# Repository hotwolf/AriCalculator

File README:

AriCalculator
=============
A homemade pocket calculator.

Directories:
============
|
+-Hardware              - Everything needed to build AriCalculator RevA, RevB,
                          and RevC
|
+-Software              - Source files (ASM and Forth) of the calculators
                          firmware
|
+-Tools                 - Tools written for the development of the AriCalculator
|
+-Subprojects           - Repository clones of the projects that AriCalculator
                          is based on

The AriCalculator software is distributed in the hope that it will be useful,
but WITHOUT ANY WARRANTY; without even the implied warranty of
MERCHANTABILITY or FITNESS FOR A PARTICULAR PURPOSE.  See the
GNU General Public License for more details.

You should have received a copy of the GNU General Public License
along with the AriCalculator software. If not, see
<http://www.gnu.org/licenses/>.

The hardware design of the Aricalculator project is licensed under a Creative
Commons Attribution-ShareAlike 3.0 Unported License
(http://creativecommons.org/licenses/by-sa/3.0/).

Hardware RevC uses Kicad library components by Walter Lain which are licensed
under a Creative Commons Attribution-ShareAlike 3.0 License 
(http://creativecommons.org/licenses/by-sa/3.0/).

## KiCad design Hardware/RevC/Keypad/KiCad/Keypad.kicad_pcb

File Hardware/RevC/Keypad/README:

Keypad
======
A general purpose key pad PCB

Directories:
============
|
+-KiCad			- KiCad project file, schematic, layout, and libraries
|
+-Gerber                - Gerber files for manufacturing

This work is licensed under a Creative Commons Attribution-ShareAlike 3.0
Unported License (http://creativecommons.org/licenses/by-sa/3.0/).

AriCalculator RevC and the Keypad use Kicad library components by Walter Lain
which are licensedunder a Creative Commons Attribution-ShareAlike 3.0 License 
(http://creativecommons.org/licenses/by-sa/3.0/).

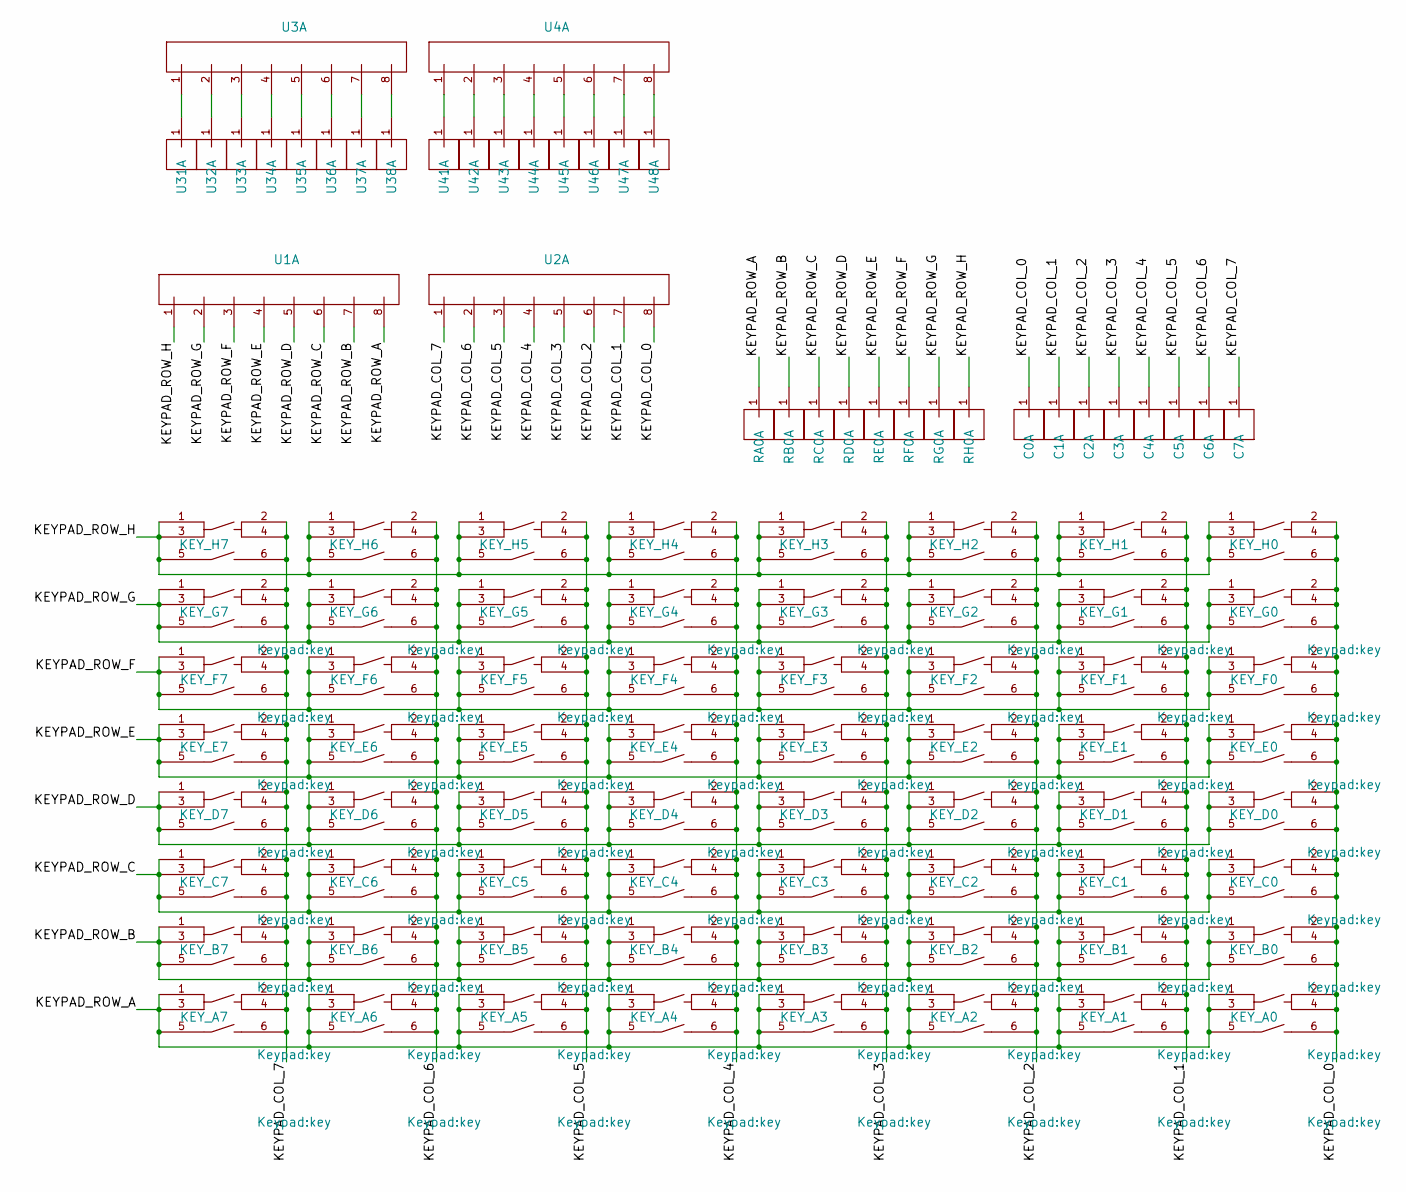
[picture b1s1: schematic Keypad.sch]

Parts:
C0, C1, C2, C3, C4, C5, C6, C7: PIN_STRIP_1; Connected_Pad
KEY_A0, KEY_A1, KEY_A2, KEY_A3, KEY_A4, KEY_A5, KEY_A6, KEY_A7: KEY; key
KEY_B0, KEY_B1, KEY_B2, KEY_B3, KEY_B4, KEY_B5, KEY_B6, KEY_B7: KEY; key
KEY_C0, KEY_C1, KEY_C2, KEY_C3, KEY_C4, KEY_C5, KEY_C6, KEY_C7: KEY; key
KEY_D0, KEY_D1, KEY_D2, KEY_D3, KEY_D4, KEY_D5, KEY_D6, KEY_D7: KEY; key
KEY_E0, KEY_E1, KEY_E2, KEY_E3, KEY_E4, KEY_E5, KEY_E6, KEY_E7: KEY; key
KEY_F0, KEY_F1, KEY_F2, KEY_F3, KEY_F4, KEY_F5, KEY_F6, KEY_F7: KEY; key
KEY_G0, KEY_G1, KEY_G2, KEY_G3, KEY_G4, KEY_G5, KEY_G6, KEY_G7: KEY; key
KEY_H0, KEY_H1, KEY_H2, KEY_H3, KEY_H4, KEY_H5, KEY_H6, KEY_H7: KEY; key
RA0: PIN_STRIP_1; Connected_Pad
RB0: PIN_STRIP_1; Connected_Pad
RC0: PIN_STRIP_1; Connected_Pad
RD0: PIN_STRIP_1; Connected_Pad
RE0: PIN_STRIP_1; Connected_Pad
RF0: PIN_STRIP_1; Connected_Pad
RG0: PIN_STRIP_1; Connected_Pad
RH0: PIN_STRIP_1; Connected_Pad
U1, U2, U3, U4: PIN_STRIP_8; pin_strip_8
U31, U32, U33, U34, U35, U36, U37, U38, U41, U42, U43, U44, U45, U46, U47, U48: PIN_STRIP_1; Connected_Pad

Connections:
/KEYPAD_COL_0: C0.1, KEY_A0.2, KEY_A0.4, KEY_A0.6, KEY_B0.2, KEY_B0.4, KEY_B0.6, KEY_C0.2, KEY_C0.4, KEY_C0.6, KEY_D0.2, KEY_D0.4, KEY_D0.6, KEY_E0.2, KEY_E0.4, KEY_E0.6, KEY_F0.2, KEY_F0.4, KEY_F0.6, KEY_G0.2, KEY_G0.4, KEY_G0.6, KEY_H0.2, KEY_H0.4, KEY_H0.6, U2.8
/KEYPAD_COL_1: C1.1, KEY_A1.2, KEY_A1.4, KEY_A1.6, KEY_B1.2, KEY_B1.4, KEY_B1.6, KEY_C1.2, KEY_C1.4, KEY_C1.6, KEY_D1.2, KEY_D1.4, KEY_D1.6, KEY_E1.2, KEY_E1.4, KEY_E1.6, KEY_F1.2, KEY_F1.4, KEY_F1.6, KEY_G1.2, KEY_G1.4, KEY_G1.6, KEY_H1.2, KEY_H1.4, KEY_H1.6, U2.7
/KEYPAD_COL_2: C2.1, KEY_A2.2, KEY_A2.4, KEY_A2.6, KEY_B2.2, KEY_B2.4, KEY_B2.6, KEY_C2.2, KEY_C2.4, KEY_C2.6, KEY_D2.2, KEY_D2.4, KEY_D2.6, KEY_E2.2, KEY_E2.4, KEY_E2.6, KEY_F2.2, KEY_F2.4, KEY_F2.6, KEY_G2.2, KEY_G2.4, KEY_G2.6, KEY_H2.2, KEY_H2.4, KEY_H2.6, U2.6
/KEYPAD_COL_3: C3.1, KEY_A3.2, KEY_A3.4, KEY_A3.6, KEY_B3.2, KEY_B3.4, KEY_B3.6, KEY_C3.2, KEY_C3.4, KEY_C3.6, KEY_D3.2, KEY_D3.4, KEY_D3.6, KEY_E3.2, KEY_E3.4, KEY_E3.6, KEY_F3.2, KEY_F3.4, KEY_F3.6, KEY_G3.2, KEY_G3.4, KEY_G3.6, KEY_H3.2, KEY_H3.4, KEY_H3.6, U2.5
/KEYPAD_COL_4: C4.1, KEY_A4.2, KEY_A4.4, KEY_A4.6, KEY_B4.2, KEY_B4.4, KEY_B4.6, KEY_C4.2, KEY_C4.4, KEY_C4.6, KEY_D4.2, KEY_D4.4, KEY_D4.6, KEY_E4.2, KEY_E4.4, KEY_E4.6, KEY_F4.2, KEY_F4.4, KEY_F4.6, KEY_G4.2, KEY_G4.4, KEY_G4.6, KEY_H4.2, KEY_H4.4, KEY_H4.6, U2.4
/KEYPAD_COL_5: C5.1, KEY_A5.2, KEY_A5.4, KEY_A5.6, KEY_B5.2, KEY_B5.4, KEY_B5.6, KEY_C5.2, KEY_C5.4, KEY_C5.6, KEY_D5.2, KEY_D5.4, KEY_D5.6, KEY_E5.2, KEY_E5.4, KEY_E5.6, KEY_F5.2, KEY_F5.4, KEY_F5.6, KEY_G5.2, KEY_G5.4, KEY_G5.6, KEY_H5.2, KEY_H5.4, KEY_H5.6, U2.3
/KEYPAD_COL_6: C6.1, KEY_A6.2, KEY_A6.4, KEY_A6.6, KEY_B6.2, KEY_B6.4, KEY_B6.6, KEY_C6.2, KEY_C6.4, KEY_C6.6, KEY_D6.2, KEY_D6.4, KEY_D6.6, KEY_E6.2, KEY_E6.4, KEY_E6.6, KEY_F6.2, KEY_F6.4, KEY_F6.6, KEY_G6.2, KEY_G6.4, KEY_G6.6, KEY_H6.2, KEY_H6.4, KEY_H6.6, U2.2
/KEYPAD_COL_7: C7.1, KEY_A7.2, KEY_A7.4, KEY_A7.6, KEY_B7.2, KEY_B7.4, KEY_B7.6, KEY_C7.2, KEY_C7.4, KEY_C7.6, KEY_D7.2, KEY_D7.4, KEY_D7.6, KEY_E7.2, KEY_E7.4, KEY_E7.6, KEY_F7.2, KEY_F7.4, KEY_F7.6, KEY_G7.2, KEY_G7.4, KEY_G7.6, KEY_H7.2, KEY_H7.4, KEY_H7.6, U2.1
/KEYPAD_ROW_A: KEY_A0.1, KEY_A0.3, KEY_A0.5, KEY_A1.1, KEY_A1.3, KEY_A1.5, KEY_A2.1, KEY_A2.3, KEY_A2.5, KEY_A3.1, KEY_A3.3, KEY_A3.5, KEY_A4.1, KEY_A4.3, KEY_A4.5, KEY_A5.1, KEY_A5.3, KEY_A5.5, KEY_A6.1, KEY_A6.3, KEY_A6.5, KEY_A7.1, KEY_A7.3, KEY_A7.5, RA0.1, U1.8
/KEYPAD_ROW_B: KEY_B0.1, KEY_B0.3, KEY_B0.5, KEY_B1.1, KEY_B1.3, KEY_B1.5, KEY_B2.1, KEY_B2.3, KEY_B2.5, KEY_B3.1, KEY_B3.3, KEY_B3.5, KEY_B4.1, KEY_B4.3, KEY_B4.5, KEY_B5.1, KEY_B5.3, KEY_B5.5, KEY_B6.1, KEY_B6.3, KEY_B6.5, KEY_B7.1, KEY_B7.3, KEY_B7.5, RB0.1, U1.7
/KEYPAD_ROW_C: KEY_C0.1, KEY_C0.3, KEY_C0.5, KEY_C1.1, KEY_C1.3, KEY_C1.5, KEY_C2.1, KEY_C2.3, KEY_C2.5, KEY_C3.1, KEY_C3.3, KEY_C3.5, KEY_C4.1, KEY_C4.3, KEY_C4.5, KEY_C5.1, KEY_C5.3, KEY_C5.5, KEY_C6.1, KEY_C6.3, KEY_C6.5, KEY_C7.1, KEY_C7.3, KEY_C7.5, RC0.1, U1.6
/KEYPAD_ROW_D: KEY_D0.1, KEY_D0.3, KEY_D0.5, KEY_D1.1, KEY_D1.3, KEY_D1.5, KEY_D2.1, KEY_D2.3, KEY_D2.5, KEY_D3.1, KEY_D3.3, KEY_D3.5, KEY_D4.1, KEY_D4.3, KEY_D4.5, KEY_D5.1, KEY_D5.3, KEY_D5.5, KEY_D6.1, KEY_D6.3, KEY_D6.5, KEY_D7.1, KEY_D7.3, KEY_D7.5, RD0.1, U1.5
/KEYPAD_ROW_E: KEY_E0.1, KEY_E0.3, KEY_E0.5, KEY_E1.1, KEY_E1.3, KEY_E1.5, KEY_E2.1, KEY_E2.3, KEY_E2.5, KEY_E3.1, KEY_E3.3, KEY_E3.5, KEY_E4.1, KEY_E4.3, KEY_E4.5, KEY_E5.1, KEY_E5.3, KEY_E5.5, KEY_E6.1, KEY_E6.3, KEY_E6.5, KEY_E7.1, KEY_E7.3, KEY_E7.5, RE0.1, U1.4
/KEYPAD_ROW_F: KEY_F0.1, KEY_F0.3, KEY_F0.5, KEY_F1.1, KEY_F1.3, KEY_F1.5, KEY_F2.1, KEY_F2.3, KEY_F2.5, KEY_F3.1, KEY_F3.3, KEY_F3.5, KEY_F4.1, KEY_F4.3, KEY_F4.5, KEY_F5.1, KEY_F5.3, KEY_F5.5, KEY_F6.1, KEY_F6.3, KEY_F6.5, KEY_F7.1, KEY_F7.3, KEY_F7.5, RF0.1, U1.3
/KEYPAD_ROW_G: KEY_G0.1, KEY_G0.3, KEY_G0.5, KEY_G1.1, KEY_G1.3, KEY_G1.5, KEY_G2.1, KEY_G2.3, KEY_G2.5, KEY_G3.1, KEY_G3.3, KEY_G3.5, KEY_G4.1, KEY_G4.3, KEY_G4.5, KEY_G5.1, KEY_G5.3, KEY_G5.5, KEY_G6.1, KEY_G6.3, KEY_G6.5, KEY_G7.1, KEY_G7.3, KEY_G7.5, RG0.1, U1.2
/KEYPAD_ROW_H: KEY_H0.1, KEY_H0.3, KEY_H0.5, KEY_H1.1, KEY_H1.3, KEY_H1.5, KEY_H2.1, KEY_H2.3, KEY_H2.5, KEY_H3.1, KEY_H3.3, KEY_H3.5, KEY_H4.1, KEY_H4.3, KEY_H4.5, KEY_H5.1, KEY_H5.3, KEY_H5.5, KEY_H6.1, KEY_H6.3, KEY_H6.5, KEY_H7.1, KEY_H7.3, KEY_H7.5, RH0.1, U1.1
unnamed: U3.1, U31.1
unnamed: U3.2, U32.1
unnamed: U3.3, U33.1
unnamed: U3.4, U34.1
unnamed: U3.5, U35.1
unnamed: U3.6, U36.1
unnamed: U3.7, U37.1
unnamed: U3.8, U38.1
unnamed: U4.1, U41.1
unnamed: U4.2, U42.1
unnamed: U4.3, U43.1
unnamed: U4.4, U44.1
unnamed: U4.5, U45.1
unnamed: U4.6, U46.1
unnamed: U4.7, U47.1
unnamed: U4.8, U48.1

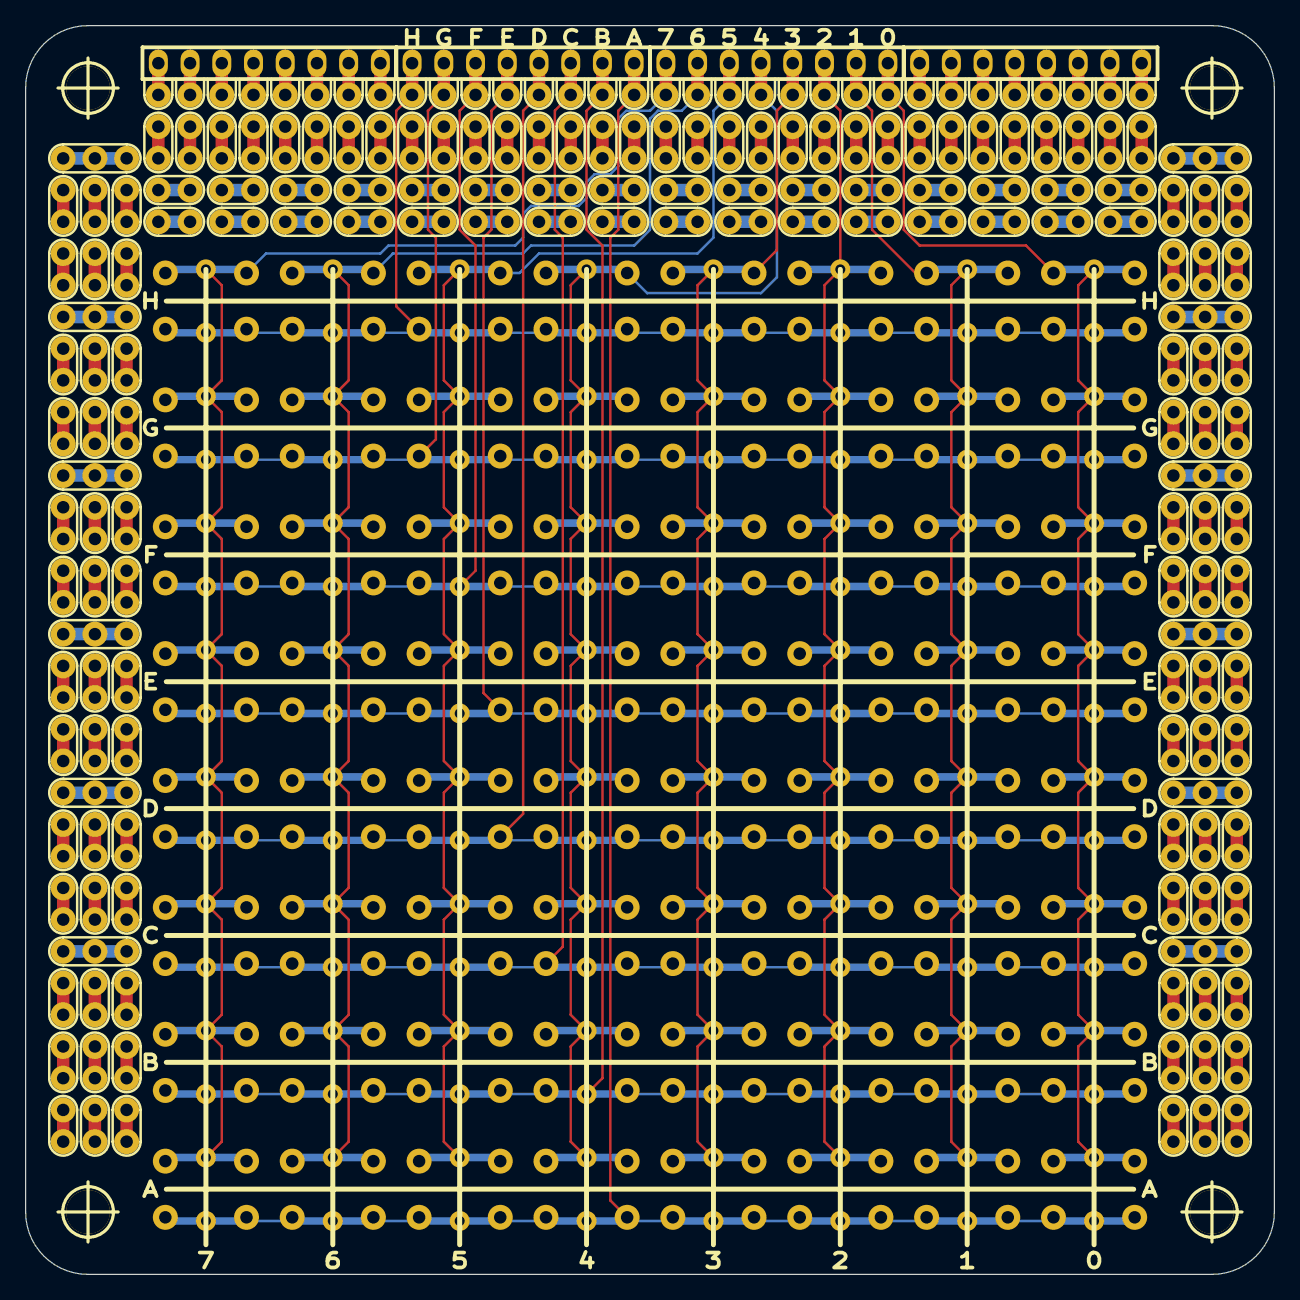
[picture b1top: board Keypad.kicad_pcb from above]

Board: 2 copper layers, 100.0 x 100.0 mm, 104 parts (0 on the bottom side), 32 nets.

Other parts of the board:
hole_3mm5, hole_3mm5#2, hole_3mm5#3, hole_3mm5#4: VAL**; hole_3mm5

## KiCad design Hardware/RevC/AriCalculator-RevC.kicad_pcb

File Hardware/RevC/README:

AriCalculator
=============
A homemade pocket calculator.

RevC is a redesign of the AriCalculator which breaks compatibility with the 
previous revisions. It is build with a single PCB instead of a combination of
S12G-Mini-EVB and millede base PCB. RevC has 38 keys (instead of 30) and
features an expansion port (SPI). All firmware development of the AriCalculator 
will be done on RevC. 

Directories:
============
|
+-Case   	        - Design files of the 3D printed case
|
+-Enclosure	        - Design files of the enclosure (for laser cutting)
|
+-PCB		        - Design files of the calculators PCB
|
+-Kepad		        - Design files of a plain key pad for debug purposes

|
+-KiCad			- KiCad project file, schematic, layout, and libraries
|
+-Gerber                - Gerber files for manufacturing

Files:
======
|
+-AriCalculator-RevC Schematic.pdf      - Schematic
|
+-AriCalculator-RevC BOM.txt            - Bill of materials
|
+-AriCalculator-RevC Assembly Plan.pdf  - Shows the location of all components
                                          to be assembled

This work is licensed under a Creative Commons Attribution-ShareAlike 3.0
Unported License (http://creativecommons.org/licenses/by-sa/3.0/).

AriCalculator RevC and the Keypad use Kicad library components by Walter Lain
which are licensedunder a Creative Commons Attribution-ShareAlike 3.0 License 
(http://creativecommons.org/licenses/by-sa/3.0/).

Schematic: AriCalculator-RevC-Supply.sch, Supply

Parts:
BAT1, BAT2: AAA-BATTERY
C3: 4.7uF
C4: 10uF
IC2: MCP1640
L1: 4.7uH
R9: 820K
R10: 470K
SW1: POWER SWITCH

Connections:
3V3: C4.1, IC2.5 (VOUT), R9.1; also elsewhere on the board
+BATT: C3.1, IC2.3 (EN), IC2.6 (VIN), L1.2, SW1.2; also elsewhere on the board
GND: BAT2.2, C3.2, C4.2, IC2.2 (GND), R10.1, SW1.1; also elsewhere on the board
unnamed: IC2.4 (VFB), R9.2, R10.2
unnamed: IC2.1 (SW), L1.1
unnamed: BAT1.1, SW1.3
unnamed: BAT1.2, BAT2.1

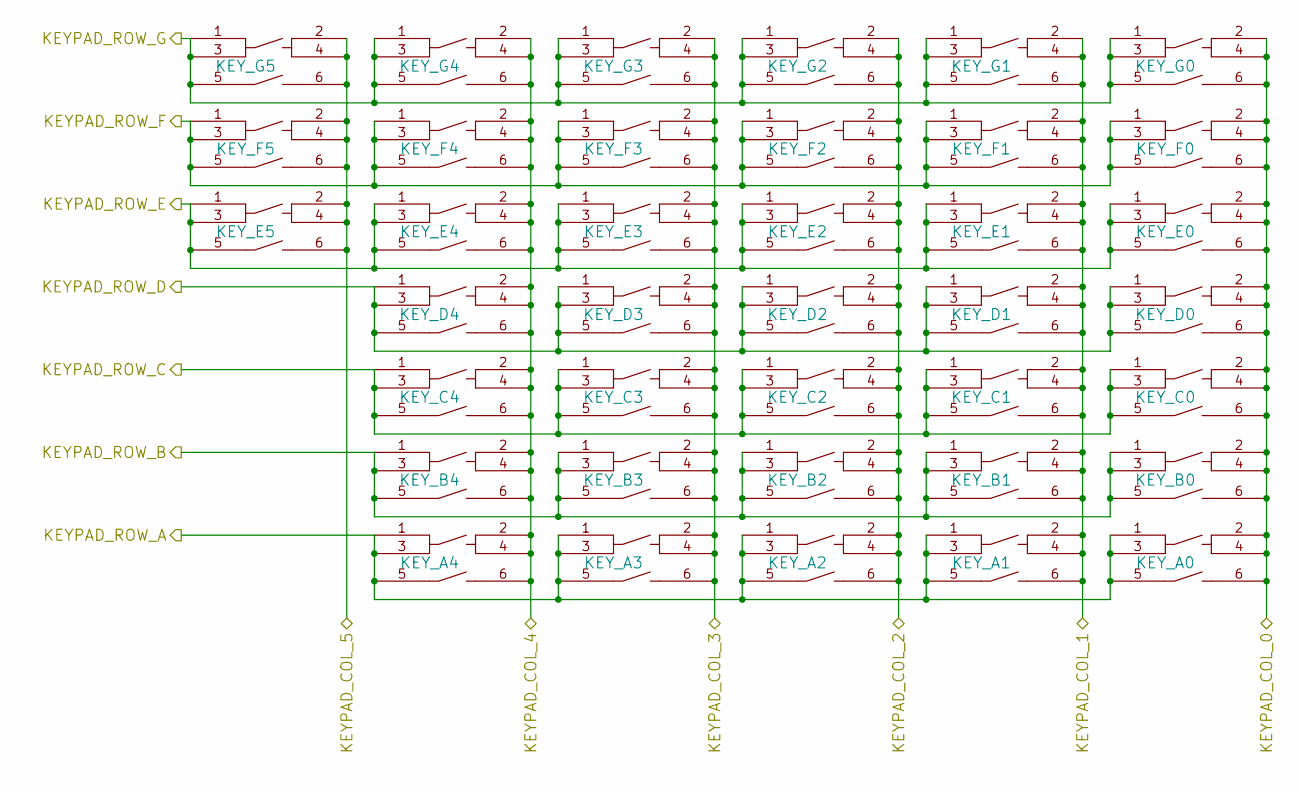
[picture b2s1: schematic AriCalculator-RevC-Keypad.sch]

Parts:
KEY_A0, KEY_A1, KEY_A2, KEY_A3, KEY_A4: KEY
KEY_B0, KEY_B1, KEY_B2, KEY_B3, KEY_B4: KEY
KEY_C0, KEY_C1, KEY_C2, KEY_C3, KEY_C4: KEY
KEY_D0, KEY_D1, KEY_D2, KEY_D3, KEY_D4: KEY
KEY_E0, KEY_E1, KEY_E2, KEY_E3, KEY_E4, KEY_E5: KEY
KEY_F0, KEY_F1, KEY_F2, KEY_F3, KEY_F4, KEY_F5: KEY
KEY_G0, KEY_G1, KEY_G2, KEY_G3, KEY_G4, KEY_G5: KEY

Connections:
/Keypad/KEYPAD_COL_0: KEY_A0.2, KEY_A0.4, KEY_A0.6, KEY_B0.2, KEY_B0.4, KEY_B0.6, KEY_C0.2, KEY_C0.4, KEY_C0.6, KEY_D0.2, KEY_D0.4, KEY_D0.6, KEY_E0.2, KEY_E0.4, KEY_E0.6, KEY_F0.2, KEY_F0.4, KEY_F0.6, KEY_G0.2, KEY_G0.4, KEY_G0.6; also elsewhere on the board
/Keypad/KEYPAD_COL_1: KEY_A1.2, KEY_A1.4, KEY_A1.6, KEY_B1.2, KEY_B1.4, KEY_B1.6, KEY_C1.2, KEY_C1.4, KEY_C1.6, KEY_D1.2, KEY_D1.4, KEY_D1.6, KEY_E1.2, KEY_E1.4, KEY_E1.6, KEY_F1.2, KEY_F1.4, KEY_F1.6, KEY_G1.2, KEY_G1.4, KEY_G1.6; also elsewhere on the board
/Keypad/KEYPAD_COL_2: KEY_A2.2, KEY_A2.4, KEY_A2.6, KEY_B2.2, KEY_B2.4, KEY_B2.6, KEY_C2.2, KEY_C2.4, KEY_C2.6, KEY_D2.2, KEY_D2.4, KEY_D2.6, KEY_E2.2, KEY_E2.4, KEY_E2.6, KEY_F2.2, KEY_F2.4, KEY_F2.6, KEY_G2.2, KEY_G2.4, KEY_G2.6; also elsewhere on the board
/Keypad/KEYPAD_COL_3: KEY_A3.2, KEY_A3.4, KEY_A3.6, KEY_B3.2, KEY_B3.4, KEY_B3.6, KEY_C3.2, KEY_C3.4, KEY_C3.6, KEY_D3.2, KEY_D3.4, KEY_D3.6, KEY_E3.2, KEY_E3.4, KEY_E3.6, KEY_F3.2, KEY_F3.4, KEY_F3.6, KEY_G3.2, KEY_G3.4, KEY_G3.6; also elsewhere on the board
/Keypad/KEYPAD_COL_4: KEY_A4.2, KEY_A4.4, KEY_A4.6, KEY_B4.2, KEY_B4.4, KEY_B4.6, KEY_C4.2, KEY_C4.4, KEY_C4.6, KEY_D4.2, KEY_D4.4, KEY_D4.6, KEY_E4.2, KEY_E4.4, KEY_E4.6, KEY_F4.2, KEY_F4.4, KEY_F4.6, KEY_G4.2, KEY_G4.4, KEY_G4.6; also elsewhere on the board
/Keypad/KEYPAD_COL_5: KEY_E5.2, KEY_E5.4, KEY_E5.6, KEY_F5.2, KEY_F5.4, KEY_F5.6, KEY_G5.2, KEY_G5.4, KEY_G5.6; also elsewhere on the board
/Keypad/KEYPAD_ROW_A: KEY_A0.1, KEY_A0.3, KEY_A0.5, KEY_A1.1, KEY_A1.3, KEY_A1.5, KEY_A2.1, KEY_A2.3, KEY_A2.5, KEY_A3.1, KEY_A3.3, KEY_A3.5, KEY_A4.1, KEY_A4.3, KEY_A4.5; also elsewhere on the board
/Keypad/KEYPAD_ROW_B: KEY_B0.1, KEY_B0.3, KEY_B0.5, KEY_B1.1, KEY_B1.3, KEY_B1.5, KEY_B2.1, KEY_B2.3, KEY_B2.5, KEY_B3.1, KEY_B3.3, KEY_B3.5, KEY_B4.1, KEY_B4.3, KEY_B4.5; also elsewhere on the board
/Keypad/KEYPAD_ROW_C: KEY_C0.1, KEY_C0.3, KEY_C0.5, KEY_C1.1, KEY_C1.3, KEY_C1.5, KEY_C2.1, KEY_C2.3, KEY_C2.5, KEY_C3.1, KEY_C3.3, KEY_C3.5, KEY_C4.1, KEY_C4.3, KEY_C4.5; also elsewhere on the board
/Keypad/KEYPAD_ROW_D: KEY_D0.1, KEY_D0.3, KEY_D0.5, KEY_D1.1, KEY_D1.3, KEY_D1.5, KEY_D2.1, KEY_D2.3, KEY_D2.5, KEY_D3.1, KEY_D3.3, KEY_D3.5, KEY_D4.1, KEY_D4.3, KEY_D4.5; also elsewhere on the board
/Keypad/KEYPAD_ROW_E: KEY_E0.1, KEY_E0.3, KEY_E0.5, KEY_E1.1, KEY_E1.3, KEY_E1.5, KEY_E2.1, KEY_E2.3, KEY_E2.5, KEY_E3.1, KEY_E3.3, KEY_E3.5, KEY_E4.1, KEY_E4.3, KEY_E4.5, KEY_E5.1, KEY_E5.3, KEY_E5.5; also elsewhere on the board
/Keypad/KEYPAD_ROW_F: KEY_F0.1, KEY_F0.3, KEY_F0.5, KEY_F1.1, KEY_F1.3, KEY_F1.5, KEY_F2.1, KEY_F2.3, KEY_F2.5, KEY_F3.1, KEY_F3.3, KEY_F3.5, KEY_F4.1, KEY_F4.3, KEY_F4.5, KEY_F5.1, KEY_F5.3, KEY_F5.5; also elsewhere on the board
/Keypad/KEYPAD_ROW_G: KEY_G0.1, KEY_G0.3, KEY_G0.5, KEY_G1.1, KEY_G1.3, KEY_G1.5, KEY_G2.1, KEY_G2.3, KEY_G2.5, KEY_G3.1, KEY_G3.3, KEY_G3.5, KEY_G4.1, KEY_G4.3, KEY_G4.5, KEY_G5.1, KEY_G5.3, KEY_G5.5; also elsewhere on the board

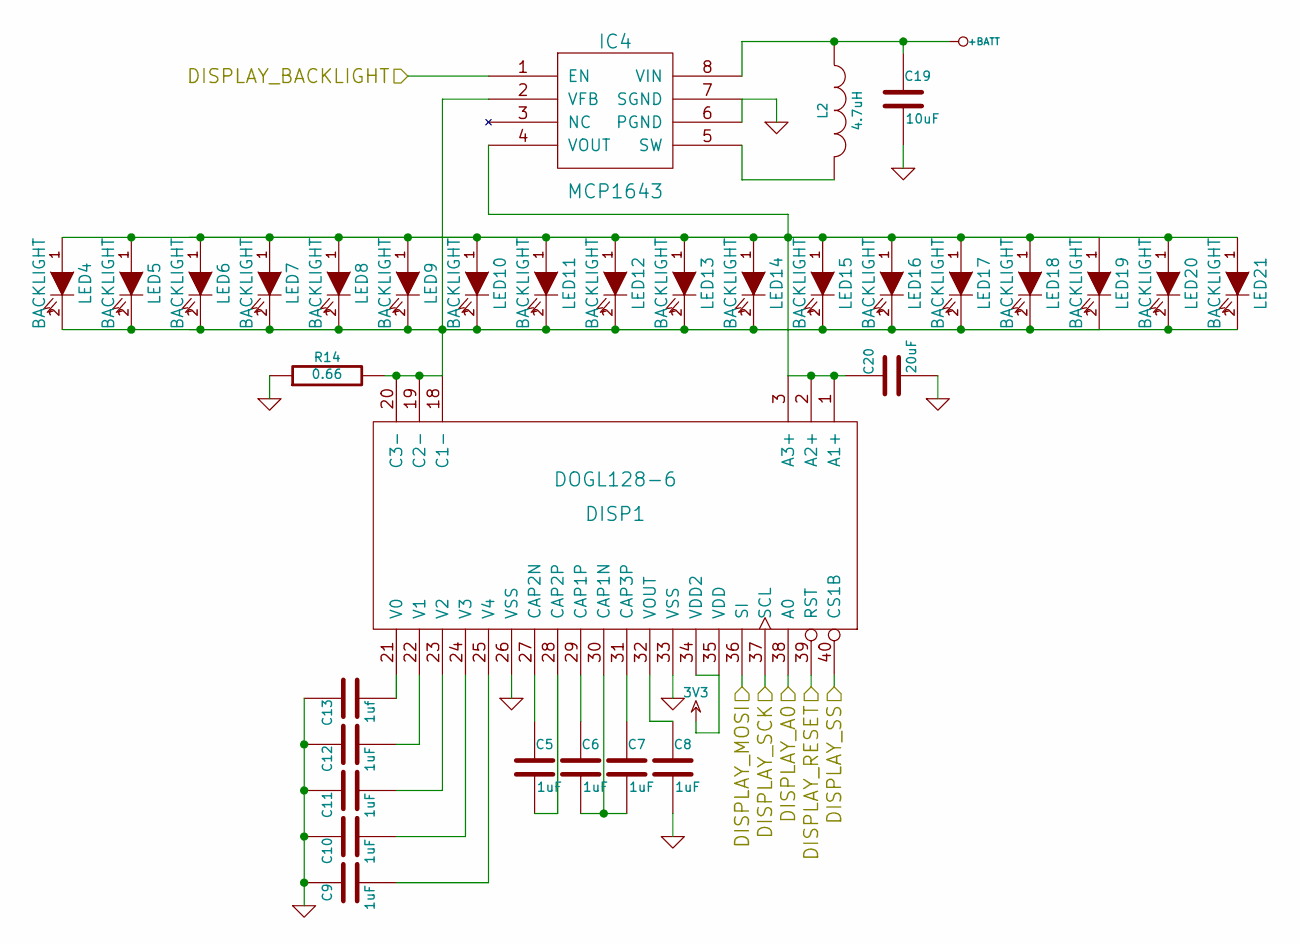
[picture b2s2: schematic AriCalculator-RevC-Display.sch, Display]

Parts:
C5, C6, C7, C8, C9, C10, C11, C12: 1uF
C13: 1uf
C19: 10uF
C20: 20uF
DISP1: DOGL128-6
IC4: MCP1643
L2: 4.7uH
LED4, LED5, LED6, LED7, LED8, LED9, LED10, LED11, LED12, LED13, LED14, LED15, LED16, LED17, LED18, LED19, LED20, LED21: BACKLIGHT
R14: 0.66

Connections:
3V3: DISP1.34 (VDD2), DISP1.35 (VDD); also elsewhere on the board
+BATT: C19.1, IC4.8 (VIN), L2.1; also elsewhere on the board
/Display/DISPLAY_A0: DISP1.38 (A0); also elsewhere on the board
/Display/DISPLAY_BACKLIGHT: IC4.1 (EN); also elsewhere on the board
/Display/DISPLAY_MOSI: DISP1.36 (SI); also elsewhere on the board
/Display/DISPLAY_RESET: DISP1.39 (RST); also elsewhere on the board
/Display/DISPLAY_SCK: DISP1.37 (SCL); also elsewhere on the board
/Display/DISPLAY_SS: DISP1.40 (CS1B); also elsewhere on the board
GND: C8.2, C9.1, C10.1, C11.1, C12.1, C13.1, C19.2, C20.2, DISP1.26 (VSS), DISP1.33 (VSS), IC4.6 (PGND), IC4.7 (SGND), R14.1; also elsewhere on the board
unnamed: C10.2, DISP1.24 (V3)
unnamed: C11.2, DISP1.23 (V2)
unnamed: C12.2, DISP1.22 (V1)
unnamed: C7.1, DISP1.31 (CAP3P)
unnamed: C5.2, DISP1.28 (CAP2P)
unnamed: C9.2, DISP1.25 (V4)
unnamed: C13.2, DISP1.21 (V0)
unnamed: C5.1, DISP1.27 (CAP2N)
unnamed: IC4.5 (SW), L2.2
unnamed: C6.1, DISP1.29 (CAP1P)
unnamed: C8.1, DISP1.32 (VOUT)
unnamed: C6.2, C7.2, DISP1.30 (CAP1N)
unnamed: DISP1.18 (C1-), DISP1.19 (C2-), DISP1.20 (C3-), IC4.2 (VFB), LED4.2 (K), LED5.2 (K), LED6.2 (K), LED7.2 (K), LED8.2 (K), LED9.2 (K), LED10.2 (K), LED11.2 (K), LED12.2 (K), LED13.2 (K), LED14.2 (K), LED15.2 (K), LED16.2 (K), LED17.2 (K), LED18.2 (K), LED19.2 (K), LED20.2 (K), LED21.2 (K), R14.2
unnamed: C20.1, DISP1.1 (A1+), DISP1.2 (A2+), DISP1.3 (A3+), IC4.4 (VOUT), LED4.1 (A), LED5.1 (A), LED6.1 (A), LED7.1 (A), LED8.1 (A), LED9.1 (A), LED10.1 (A), LED11.1 (A), LED12.1 (A), LED13.1 (A), LED14.1 (A), LED15.1 (A), LED16.1 (A), LED17.1 (A), LED18.1 (A), LED19.1 (A), LED20.1 (A), LED21.1 (A)

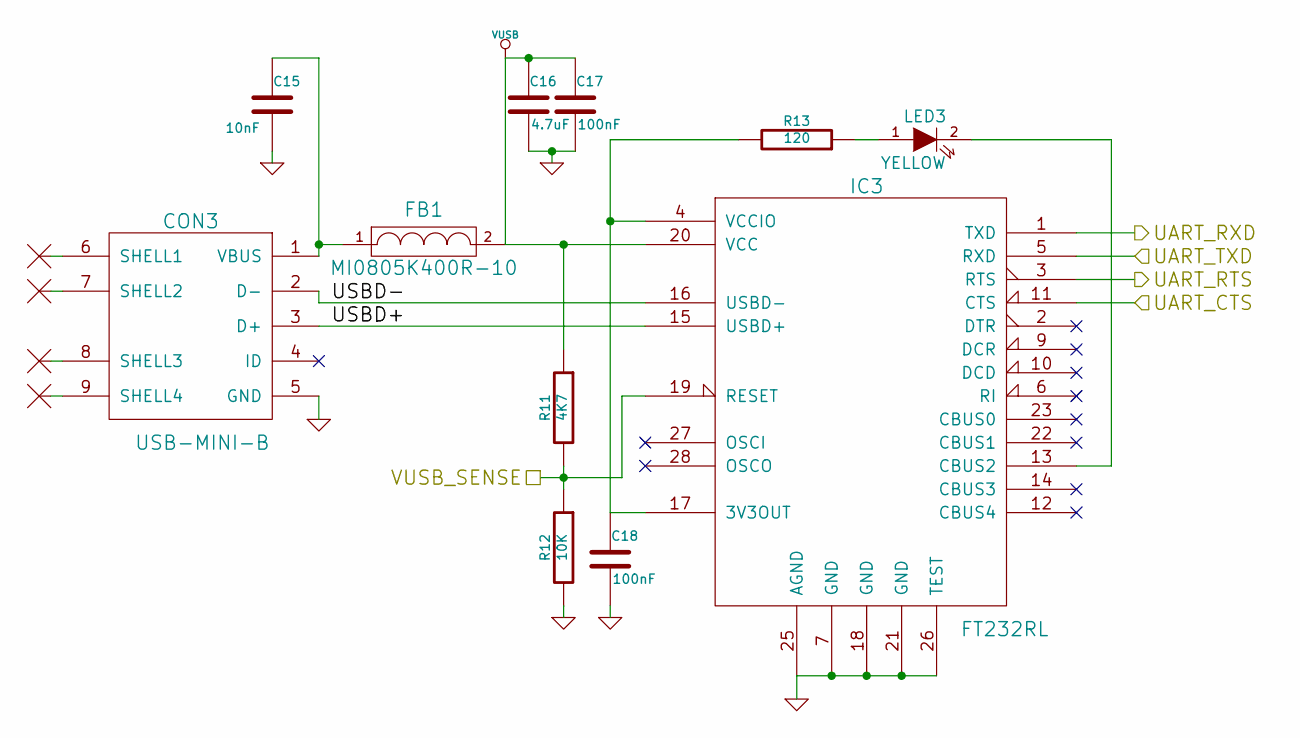
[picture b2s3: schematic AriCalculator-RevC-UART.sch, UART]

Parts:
C15: 10nF
C16: 4.7uF
C17, C18: 100nF
CON3: USB-MINI-B
FB1: MI0805K400R-10
IC3: FT232RL
LED3: YELLOW
NC1, NC2, NC3, NC4: NC
R11: 4K7
R12: 10K
R13: 120

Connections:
/MCU/UART_CTS: IC3.11 (CTS); also elsewhere on the board
/MCU/UART_RTS: IC3.3 (RTS); also elsewhere on the board
/MCU/UART_RXD: IC3.1 (TXD); also elsewhere on the board
/MCU/UART_TXD: IC3.5 (RXD); also elsewhere on the board
/MCU/VUSB_SENSE: IC3.19 (RESET), R11.2, R12.1; also elsewhere on the board
/UART/USBD+: CON3.3 (D+), IC3.15 (USBD+)
/UART/USBD-: CON3.2 (D-), IC3.16 (USBD-)
GND: C15.2, C16.2, C17.2, C18.2, CON3.5 (GND), IC3.7 (GND), IC3.18 (GND), IC3.21 (GND), IC3.25 (AGND), IC3.26 (TEST), R12.2; also elsewhere on the board
unnamed: CON3.9 (SHELL4), NC4.~
unnamed: CON3.6 (SHELL1), NC1.~
unnamed: CON3.7 (SHELL2), NC2.~
unnamed: CON3.8 (SHELL3), NC3.~
unnamed: C15.1, CON3.1 (VBUS), FB1.1
unnamed: C18.1, IC3.4 (VCCIO), IC3.17 (3V3OUT), R13.2
unnamed: LED3.1 (A), R13.1
unnamed: IC3.13 (CBUS2), LED3.2 (K)
VUSB: C16.1, C17.1, FB1.2, IC3.20 (VCC), R11.1

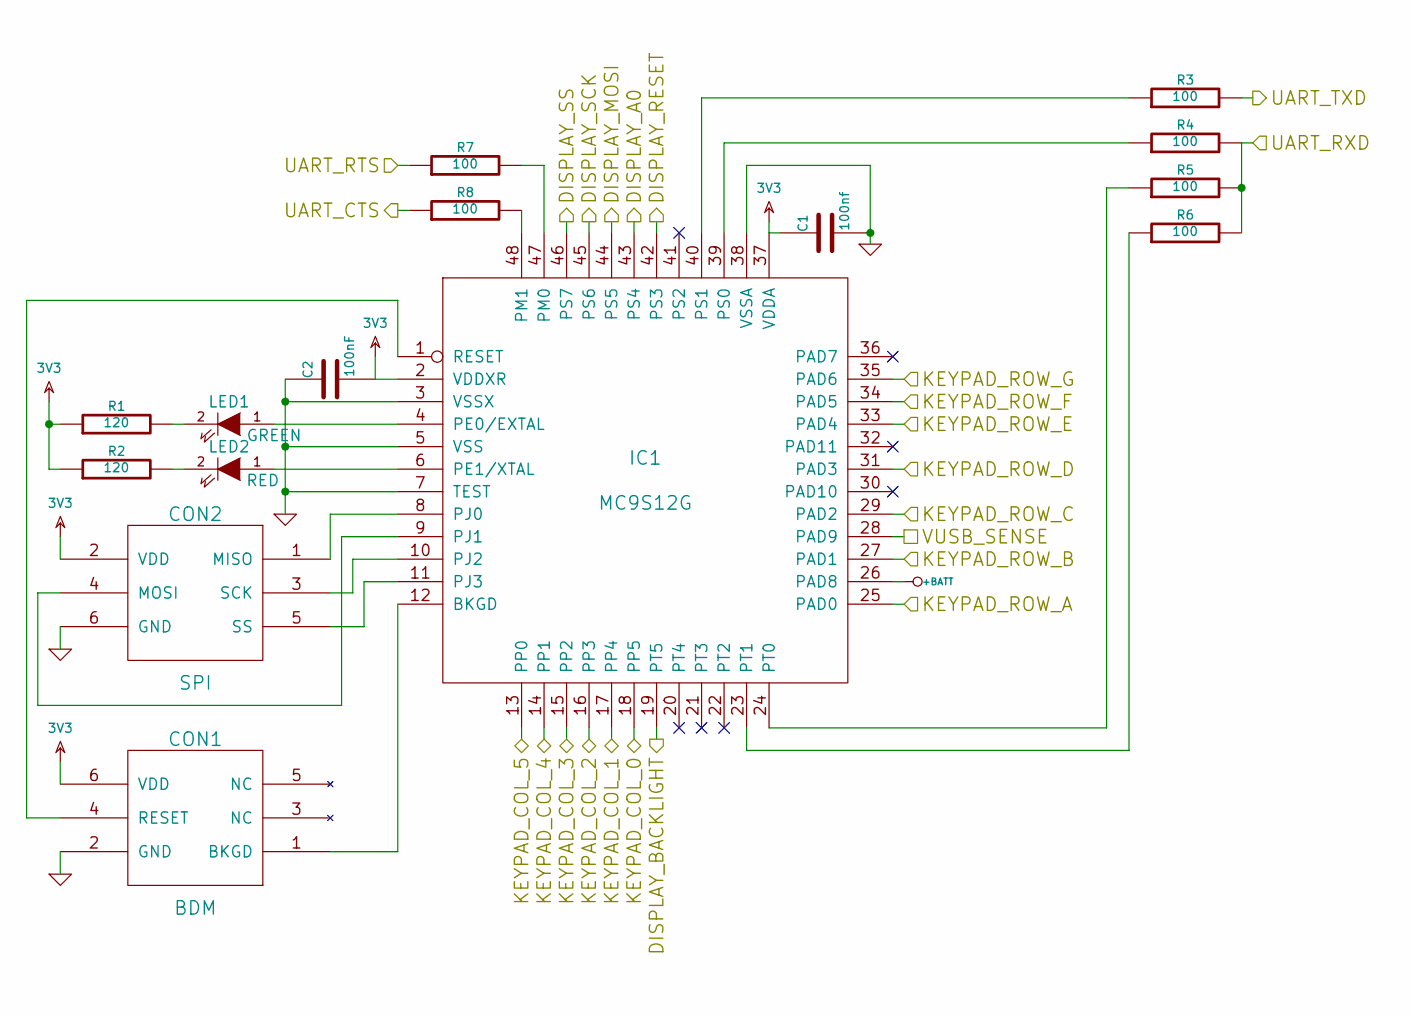
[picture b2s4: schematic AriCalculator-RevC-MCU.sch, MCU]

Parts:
C1: 100nf
C2: 100nF
CON1: BDM
CON2: SPI
IC1: MC9S12G
LED1: GREEN
LED2: RED
R1, R2: 120
R3, R4, R5, R6, R7, R8: 100

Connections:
3V3: C1.1, C2.2, CON1.6 (VDD), CON2.2 (VDD), IC1.2 (VDDXR), IC1.37 (VDDA), R1.1, R2.1; also elsewhere on the board
+BATT: IC1.26 (PAD8); also elsewhere on the board
/Display/DISPLAY_A0: IC1.43 (PS4); also elsewhere on the board
/Display/DISPLAY_BACKLIGHT: IC1.19 (PT5); also elsewhere on the board
/Display/DISPLAY_MOSI: IC1.44 (PS5); also elsewhere on the board
/Display/DISPLAY_RESET: IC1.42 (PS3); also elsewhere on the board
/Display/DISPLAY_SCK: IC1.45 (PS6); also elsewhere on the board
/Display/DISPLAY_SS: IC1.46 (PS7); also elsewhere on the board
/Keypad/KEYPAD_COL_0: IC1.18 (PP5); also elsewhere on the board
/Keypad/KEYPAD_COL_1: IC1.17 (PP4); also elsewhere on the board
/Keypad/KEYPAD_COL_2: IC1.16 (PP3); also elsewhere on the board
/Keypad/KEYPAD_COL_3: IC1.15 (PP2); also elsewhere on the board
/Keypad/KEYPAD_COL_4: IC1.14 (PP1); also elsewhere on the board
/Keypad/KEYPAD_COL_5: IC1.13 (PP0); also elsewhere on the board
/Keypad/KEYPAD_ROW_A: IC1.25 (PAD0); also elsewhere on the board
/Keypad/KEYPAD_ROW_B: IC1.27 (PAD1); also elsewhere on the board
/Keypad/KEYPAD_ROW_C: IC1.29 (PAD2); also elsewhere on the board
/Keypad/KEYPAD_ROW_D: IC1.31 (PAD3); also elsewhere on the board
/Keypad/KEYPAD_ROW_E: IC1.33 (PAD4); also elsewhere on the board
/Keypad/KEYPAD_ROW_F: IC1.34 (PAD5); also elsewhere on the board
/Keypad/KEYPAD_ROW_G: IC1.35 (PAD6); also elsewhere on the board
/MCU/UART_CTS: R8.1; also elsewhere on the board
/MCU/UART_RTS: R7.1; also elsewhere on the board
/MCU/UART_RXD: R4.2, R5.2, R6.2; also elsewhere on the board
/MCU/UART_TXD: R3.2; also elsewhere on the board
/MCU/VUSB_SENSE: IC1.28 (PAD9); also elsewhere on the board
GND: C1.2, C2.1, CON1.2 (GND), CON2.6 (GND), IC1.3 (VSSX), IC1.5 (VSS), IC1.7 (TEST), IC1.38 (VSSA); also elsewhere on the board
unnamed: CON2.4 (MOSI), IC1.9 (PJ1)
unnamed: LED1.2 (K), R1.2
unnamed: CON2.1 (MISO), IC1.8 (PJ0)
unnamed: CON2.3 (SCK), IC1.10 (PJ2)
unnamed: CON1.1 (BKGD), IC1.12 (BKGD)
unnamed: CON2.5 (SS), IC1.11 (PJ3)
unnamed: LED2.2 (K), R2.2
unnamed: IC1.23 (PT1), R6.1
unnamed: IC1.40 (PS1), R3.1
unnamed: IC1.6 (PE1/XTAL), LED2.1 (A)
unnamed: IC1.4 (PE0/EXTAL), LED1.1 (A)
unnamed: CON1.4 (RESET), IC1.1 (RESET)
unnamed: IC1.48 (PM1), R8.2
unnamed: IC1.47 (PM0), R7.2
unnamed: IC1.24 (PT0), R5.1
unnamed: IC1.39 (PS0), R4.1

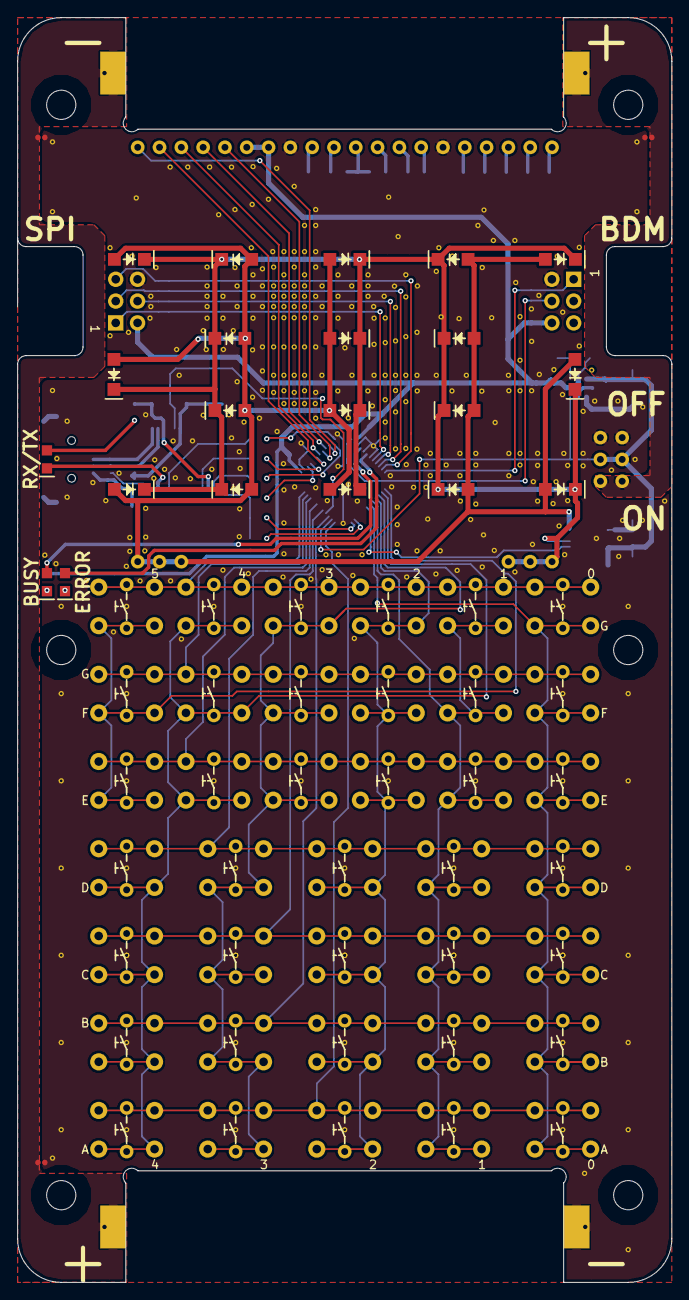
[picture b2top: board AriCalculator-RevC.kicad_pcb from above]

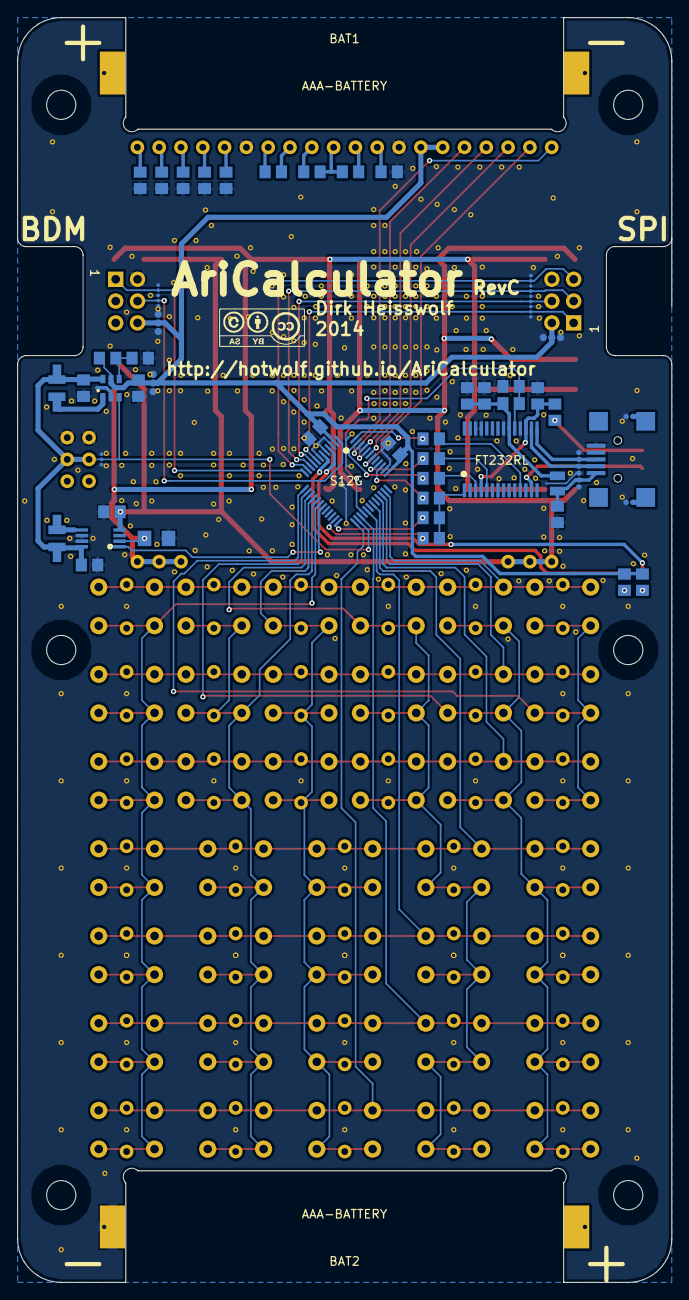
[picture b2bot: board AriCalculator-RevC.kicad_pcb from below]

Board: 2 copper layers, 76.2 x 147.3 mm, 149 parts (82 on the bottom side), 68 nets.

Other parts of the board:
SG: 0.8; spark_gap_pad_0.8
SG#2, SG#3, SG#4, SG#5, SG#6, SG#7, SG#8, SG#9, SG#10, SG#11, SG#12: 0.8; spark_gap_pad_0.8
SG#13, SG#14, SG#15, SG#16, SG#17, SG#18, SG#19, SG#20, SG#21: 1.0; spark_gap_pad_1.0
SG#22, SG#23, SG#24, SG#25, SG#26, SG#27, SG#28, SG#29, SG#30, SG#31, SG#32, SG#33, SG#34, SG#35, SG#36, SG#37, SG#38: 0.6; spark_gap_pad_0.6
enclosure: AriCalculator; enclosure
spark_gap_pad_0.8, spark_gap_pad_0.8#2, spark_gap_pad_0.8#3, spark_gap_pad_0.8#4: SG; spark_gap_pad_0.8

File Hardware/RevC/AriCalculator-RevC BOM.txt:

Bill of Materials for the AriCalculator RevC:
=============================================

ICs:

1x      MC9S12G...LF            48LQFP                  IC1
1x      MCP1640(C)              SOT23-6                 IC2             
1x      FT232RL                 SSOP-28                 IC3
1x      MCP1643                 MSOP-8                  IC4 (optional)

Capacitors:

1x       10nF                   0805                    C15
5x      100nF                   0805                    C1, C2, C17, C18, C21 
9x        1uF                   0805                    C5, C6, C7, C8, C9, C10, C11, C12, C13
2x      4.7uF                   0805                    C3, C16
2x       10uF                   0805                    C4, C19 (optional)
1x       20uF                   0805                    C20 (optional)

Inductors:

1x       10nH                   0805                    FB1
2x      4.7uH                   LQH3C                   L1, L2 (optional)

Resistors:

1x       0.66                   1206                    R14 (optional)
6x        100                   0805                    R3, R4, R5, R6, R7, R8
3x        120                   0805                    R1, R2, R13
1x       4.7K                   0805                    R11
1x        10K                   0805                    R12
1x       470K                   0805                    R10
1x       820K                   0805                    R9

LEDs:

1x      red                     0805                    LED3
1x      green                   0805                    LED2
1x      yellow                  0805                    LED1
18x     backlight               1206                    LED3..LED21 (all optional)
1x      EA LED68x51             print                   (optional)

Display:

1x      EA DOGL128-6            print                   DISP1

Buttons and switches:

1x      switch                  print                   SW1
38x     button                  print (6mmx6mm)         KEY_A0..KEY_G5

Connectors:

2x      2X3  bent               print                   CON1, CON2
1x      USB-Mini-B              SMD                     CON3

Battery Holders:

2x      AAA-battery             AAA size                BAT1, BAT2

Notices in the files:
Hardware/RevC/Keypad/KiCad/Keypad.kicad_pcb:
CC BY-SA
